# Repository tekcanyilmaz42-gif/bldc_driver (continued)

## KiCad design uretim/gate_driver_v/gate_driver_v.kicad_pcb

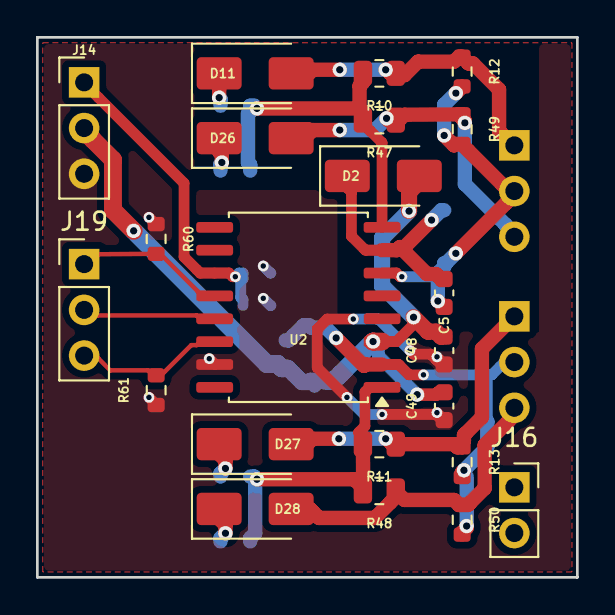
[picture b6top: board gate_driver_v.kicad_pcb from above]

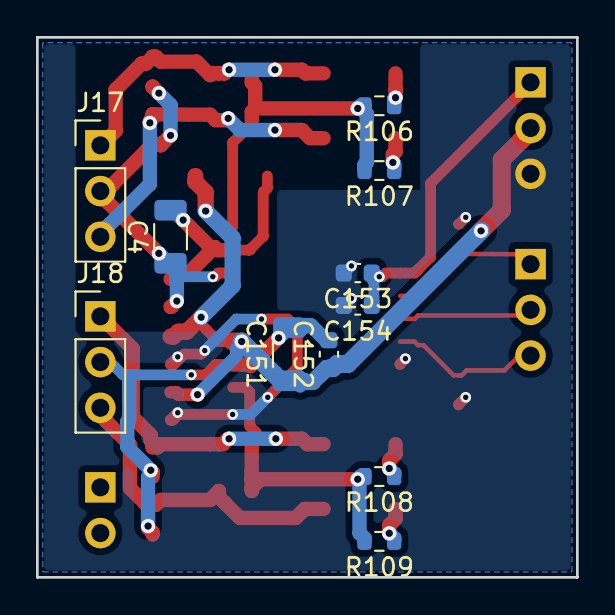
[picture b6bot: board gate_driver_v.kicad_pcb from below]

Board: 2 copper layers, 30.0 x 30.0 mm, 33 parts (11 on the bottom side), 19 nets.

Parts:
C4: 2.2uF/25V; C_1206_3216Metric
C5, C152, C153: 100nF; C_0603_1608Metric
C48, C49, C154: 1uF; C_0603_1608Metric
C151: 22uF/25V; C_1206_3216Metric
D2: US1D; D_SMA
D11, D26, D27, D28: SS18; D_SMA
J14: Pwr_V; PinHeader_1x03_P2.54mm_Vertical
J16: Sense_V_stack; PinSocket_1x02_P2.54mm_Vertical
J17: Gate_H_V; PinHeader_1x03_P2.54mm_Vertical
J18: Gate_L_V; PinHeader_1x03_P2.54mm_Vertical
J19: Ctrl_V; PinHeader_1x03_P2.54mm_Vertical
R10, R11, R47, R48: 10; R_0805_2012Metric
R12, R13, R49, R50, R60, R61: 10k; R_0603_1608Metric
R106, R107, R108, R109: 2.2; R_0603_1608Metric
U2: IR2110S; SOIC-16W_7.5x10.3mm_P1.27mm

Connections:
3V3_IO: C153.1, C154.1, J14.1, U2.11 (VDD)
12V: C48.2, C49.2, C151.1, C152.1, D2.2 (A), J14.2, U2.3 (VCC)
/Katman2_GateDriver_V/HO_V: R10.1, R47.1, R106.2, R107.2, U2.8 (HO)
/Katman2_GateDriver_V/HO_V_OFF_D11: D11.1 (K), R106.1
/Katman2_GateDriver_V/HO_V_OFF_D26: D26.1 (K), R107.1
/Katman2_GateDriver_V/LO_V: R11.1, R48.1, R108.2, R109.2, U2.1 (LO)
/Katman2_GateDriver_V/LO_V_OFF_D27: D27.1 (K), R108.1
/Katman2_GateDriver_V/LO_V_OFF_D28: D28.1 (K), R109.1
/Katman2_GateDriver_V/VB_V: C4.2, C5.2, D2.1 (K), U2.7 (VB)
GND: C48.1, C49.1, C153.2, C154.2, J14.3, R60.2, R61.1, U2.15 (VSS)
G_VH1: D11.2 (A), J17.1, R10.2, R12.2
G_VH2: D26.2 (A), J17.3, R47.2, R49.2
G_VH_IN: J19.1, R60.1, U2.12 (HIN)
G_VL1: D27.2 (A), J18.1, R11.2, R13.2
G_VL2: D28.2 (A), J18.3, R48.2, R50.2
G_VL_IN: J19.3, R61.2, U2.14 (LIN)
Phase_V: C4.1, C5.1, J17.2, R12.1, R49.1, U2.6 (VS)
SD: J19.2, U2.13 (SD)
VSH: C151.2, C152.2, J18.2, R13.1, R50.1, U2.2 (COM)
